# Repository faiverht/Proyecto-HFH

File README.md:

# Proyecto-HFH

## Avance placa primera versión:
Tarjeta de expansión de puertos análogos con conversor análogo digital MCP3424 (4 canales de 18 bits, PGA:1, 2, 4, 8), comunicación I2C dirección I2C (default): 1101

## Frontal

## Trasera

## Otras

## Terminado

## Configuración de Jumpers para fuente de alimetación

Alimentación de voltaje configurable:

1 - Desde la placa arduino Uno 5V (Jumper JP_VDC1 cualquiera o sin conexión y jumper V_IN1 en posición 'INO 5V')

2 - Desde fuente externa mediante Jack 12V (Jumper JP_VDC1  en posición '12V JACK' y jumper V_IN1 en posición 'REG 5V')

3 - Desde fuente externa mediante bornera 12V (Jumper JP_VDC1  en posición '12V EXT' y jumper V_IN1 en posición 'REG 5V')

Adicionalmente los conectores J2, J3 y J4 tienen alimentación configurable de 5V o 12V según posición de los jumpers DC2, DC3 y DC4

**Nota:**

El conector J1 se utiliza exclusivamente para sensor de entrada con alimentación de 6V

## Tarjeta de expansión terminada y en funcionamiento
EL código de prueba para Arduino se encuentran disponibles en /Arduino/Code pruebas de este mismo repositorio

Arduino y tarjeta de expansión

Montajes

Prueba de montaje y adquisición con sensor de gas MQ4

## Proyecto de monitoreo y control con Arduino y/o Raspberry Pi y/o PC (Win - Linux)

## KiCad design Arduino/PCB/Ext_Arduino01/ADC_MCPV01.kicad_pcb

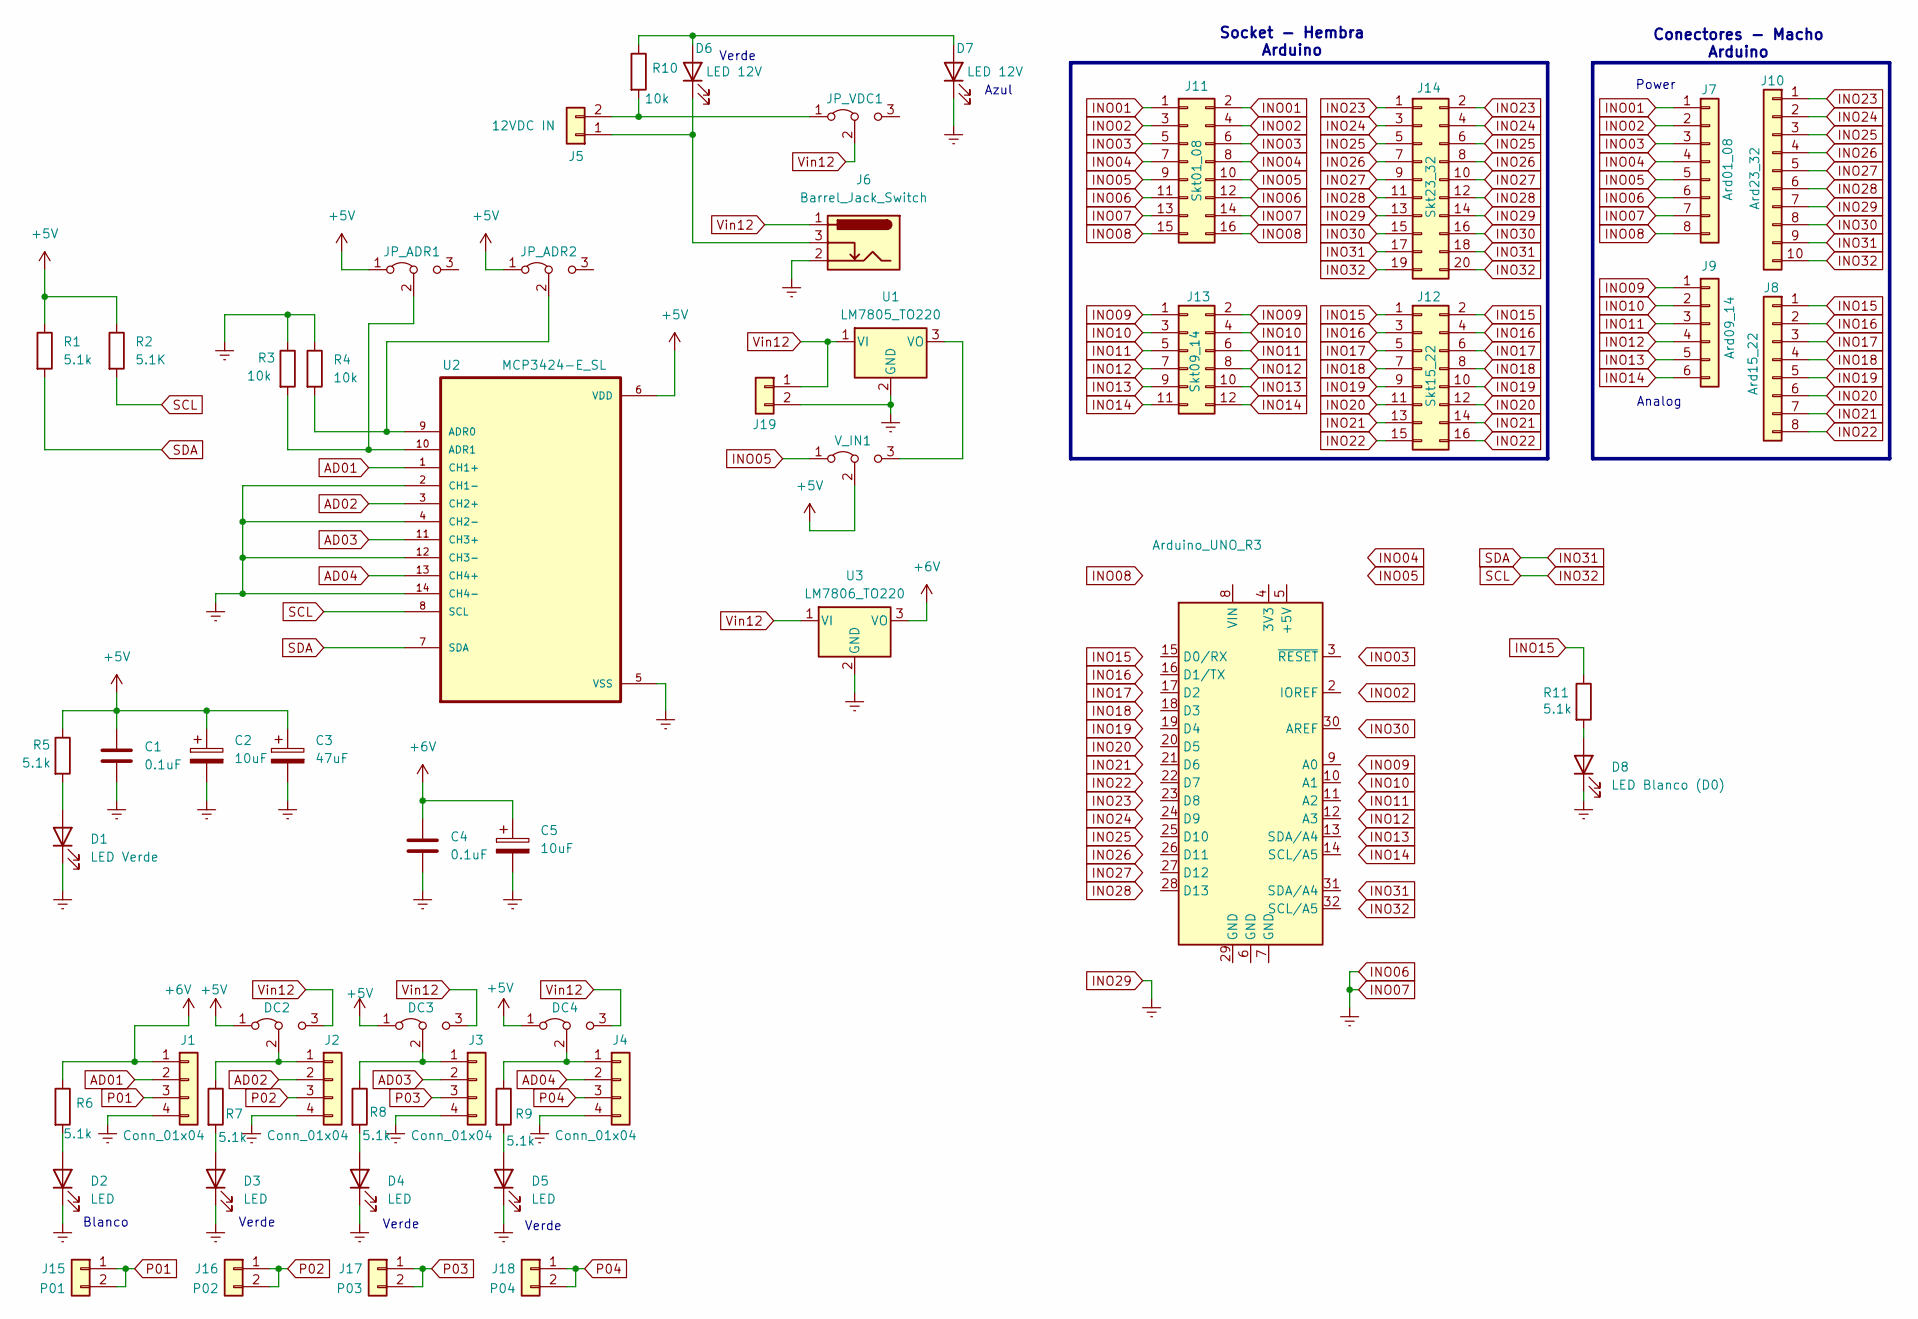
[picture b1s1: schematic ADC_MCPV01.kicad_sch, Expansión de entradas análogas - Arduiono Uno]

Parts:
A1: Arduino_UNO_R3
C1, C4: 0.1uF; C_0603_1608Metric
C2, C5: 10uF; C_1206_3216Metric
C3: 47uF; CP_Elec_6.3x5.9
D1: LED Verde; LED_0603_1608Metric_Pad1.05x0.95mm_HandSolder
D2, D3, D4, D5: LED; LED_0603_1608Metric_Pad1.05x0.95mm_HandSolder
D6, D7: LED 12V; LED_0603_1608Metric_Pad1.05x0.95mm_HandSolder
D8: LED Blanco (D0); LED_0603_1608Metric_Pad1.05x0.95mm_HandSolder
DC2, DC3, DC4: Jumper_3_Bridged12; PinHeader_1x03_P2.54mm_Vertical
J1, J2, J3, J4: Conn_01x04; Molex_KK-254_AE-6410-04A_1x04_P2.54mm_Vertical
J5: 12VDC IN; TerminalBlock_Phoenix_MKDS-1,5-2-5.08_1x02_P5.08mm_Horizont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
J6: Barrel_Jack_Switch; BarrelJack_Horizontal
J7: Ard01_08; PinHeader_1x08_P2.54mm_Vertical
J8: Ard15_22; PinHeader_1x08_P2.54mm_Vertical
J9: Ard09_14; PinHeader_1x06_P2.54mm_Vertical
J10: Ard23_32; PinHeader_1x10_P2.54mm_Vertical
J11: Skt01_08; PinSocket_2x08_P2.54mm_Vertical
J12: Skt15_22; PinSocket_2x08_P2.54mm_Vertical
J13: Skt09_14; PinSocket_2x06_P2.54mm_Vertical
J14: Skt23_32; PinSocket_2x10_P2.54mm_Vertical
J15: P01; PinSocket_1x02_P2.54mm_Vertical
J16: P02; PinSocket_1x02_P2.54mm_Vertical
J17: P03; PinSocket_1x02_P2.54mm_Vertical
J18: P04; PinSocket_1x02_P2.54mm_Vertical
J19: 12VDC IN; PinSocket_1x02_P2.54mm_Vertical
JP_ADR1, JP_ADR2: Jumper_3_Bridged12; PinHeader_1x03_P2.54mm_Vertical
JP_VDC1: Jumper_3_Bridged12; PinHeader_1x03_P2.54mm_Vertical
R1, R5, R6, R7, R8, R9, R11: 5.1k; R_1206_3216Metric
R2: 5.1K; R_1206_3216Metric
R3, R4, R10: 10k; R_1206_3216Metric
U1: LM7805_TO220; TO229P990X238-3N
U2: MCP3424-E_SL; SOIC-14_3.9x8.7mm_P1.27mm; DigiKey_Part_Number MCP3424-E/SL-ND
U3: LM7806_TO220; TO-220-3_Vertical
V_IN1: Jumper_3_Bridged12; PinHeader_1x03_P2.54mm_Vertical

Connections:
+5V: C1.1, C2.1, C3.1, DC2.1 (A), DC3.1 (A), DC4.1 (A), JP_ADR1.1 (A), JP_ADR2.1 (A), R1.1, R2.1, R5.1, U2.6 (VDD), V_IN1.2 (C)
+6V: C4.1, C5.1, J1.1, R6.1, U3.3 (VO)
AD01: J1.2, U2.1 (CH1+)
AD02: J2.2, U2.3 (CH2+)
AD03: J3.2, U2.11 (CH3+)
AD04: J4.2, U2.13 (CH4+)
INO01: J7.1, J11.1, J11.2
INO02: J7.2, J11.3, J11.4
INO03: J7.3, J11.5, J11.6
INO04: J7.4, J11.7, J11.8
INO05: J7.5, J11.9, J11.10, V_IN1.1 (A)
INO06: C1.2, C2.2, C3.2, C4.2, C5.2, D1.1 (K), D2.1 (K), D3.1 (K), D4.1 (K), D5.1 (K), D7.1 (K), D8.1 (K), J1.4, J2.4, J3.4, J4.4, J6.2, J7.6, J7.7, J10.7, J11.11, J11.12, J11.13, J11.14, J14.13, J14.14, J19.2, R3.1, R4.1, U1.2 (GND), U2.2 (CH1-), U2.4 (CH2-), U2.5 (VSS), U2.12 (CH3-), U2.14 (CH4-), U3.2 (GND)
INO08: J7.8, J11.15, J11.16
INO09: J9.1, J13.1, J13.2
INO10: J9.2, J13.3, J13.4
INO11: J9.3, J13.5, J13.6
INO12: J9.4, J13.7, J13.8
INO13: J9.5, J13.9, J13.10
INO14: J9.6, J13.11, J13.12
INO15: J8.1, J12.1, J12.2, R11.1
INO16: J8.2, J12.3, J12.4
INO17: J8.3, J12.5, J12.6
INO18: J8.4, J12.7, J12.8
INO19: J8.5, J12.9, J12.10
INO20: J8.6, J12.11, J12.12
INO21: J8.7, J12.13, J12.14
INO22: J8.8, J12.15, J12.16
INO23: J10.1, J14.1, J14.2
INO24: J10.2, J14.3, J14.4
INO25: J10.3, J14.5, J14.6
INO26: J10.4, J14.7, J14.8
INO27: J10.5, J14.9, J14.10
INO28: J10.6, J14.11, J14.12
INO30: J10.8, J14.15, J14.16
INO31: J10.9, J14.17, J14.18, R1.2, U2.7 (SDA)
INO32: J10.10, J14.19, J14.20, R2.2, U2.8 (SCL)
unnamed: D1.2 (A), R5.2
unnamed: D2.2 (A), R6.2
unnamed: D3.2 (A), R7.2
unnamed: D4.2 (A), R8.2
unnamed: D5.2 (A), R9.2
unnamed: D6.2 (A), D7.2 (A), R10.1
unnamed: D6.1 (K), J5.1, J6.3
unnamed: D8.2 (A), R11.2
unnamed: DC2.2 (C), J2.1, R7.1
unnamed: DC3.2 (C), J3.1, R8.1
unnamed: DC4.2 (C), J4.1, R9.1
unnamed: J5.2, JP_VDC1.1 (A), R10.2
unnamed: JP_ADR1.2 (C), R3.2, U2.10 (ADR1)
unnamed: JP_ADR2.2 (C), R4.2, U2.9 (ADR0)
unnamed: U1.3 (VO), V_IN1.3 (B)
P01: J1.3, J15.1, J15.2
P02: J2.3, J16.1, J16.2
P03: J3.3, J17.1, J17.2
P04: J4.3, J18.1, J18.2
Vin12: DC2.3 (B), DC3.3 (B), DC4.3 (B), J6.1, J19.1, JP_VDC1.2 (C), U1.1 (VI), U3.1 (VI)

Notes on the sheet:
Analog
Verde
Blanco
Azul
Power
Socket - Hembra Arduino
Conectores - Macho Arduino

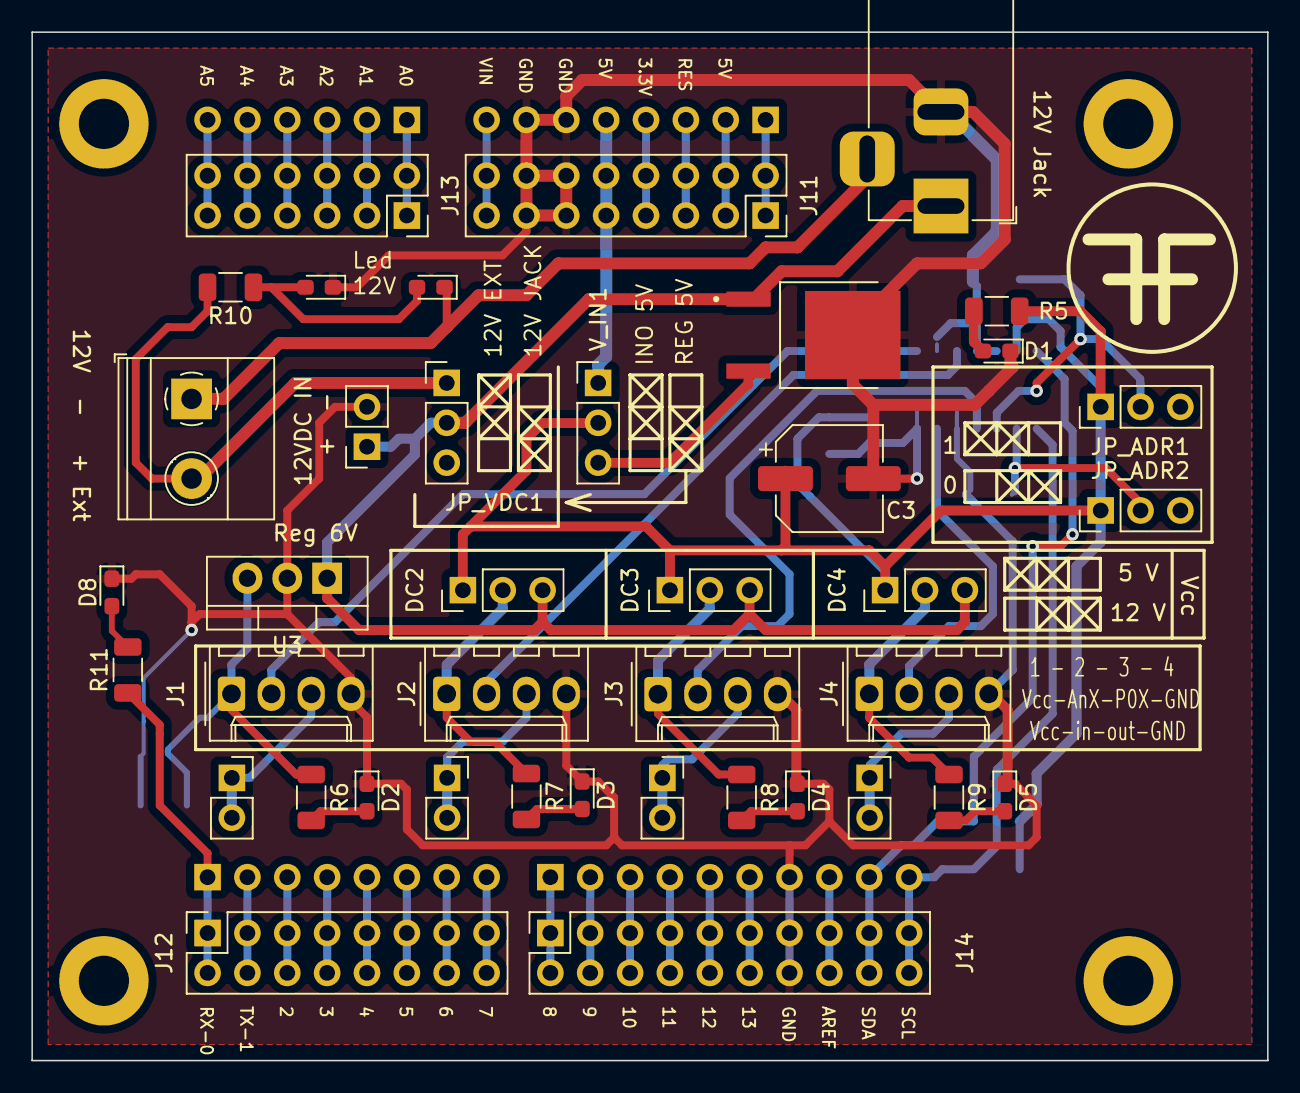
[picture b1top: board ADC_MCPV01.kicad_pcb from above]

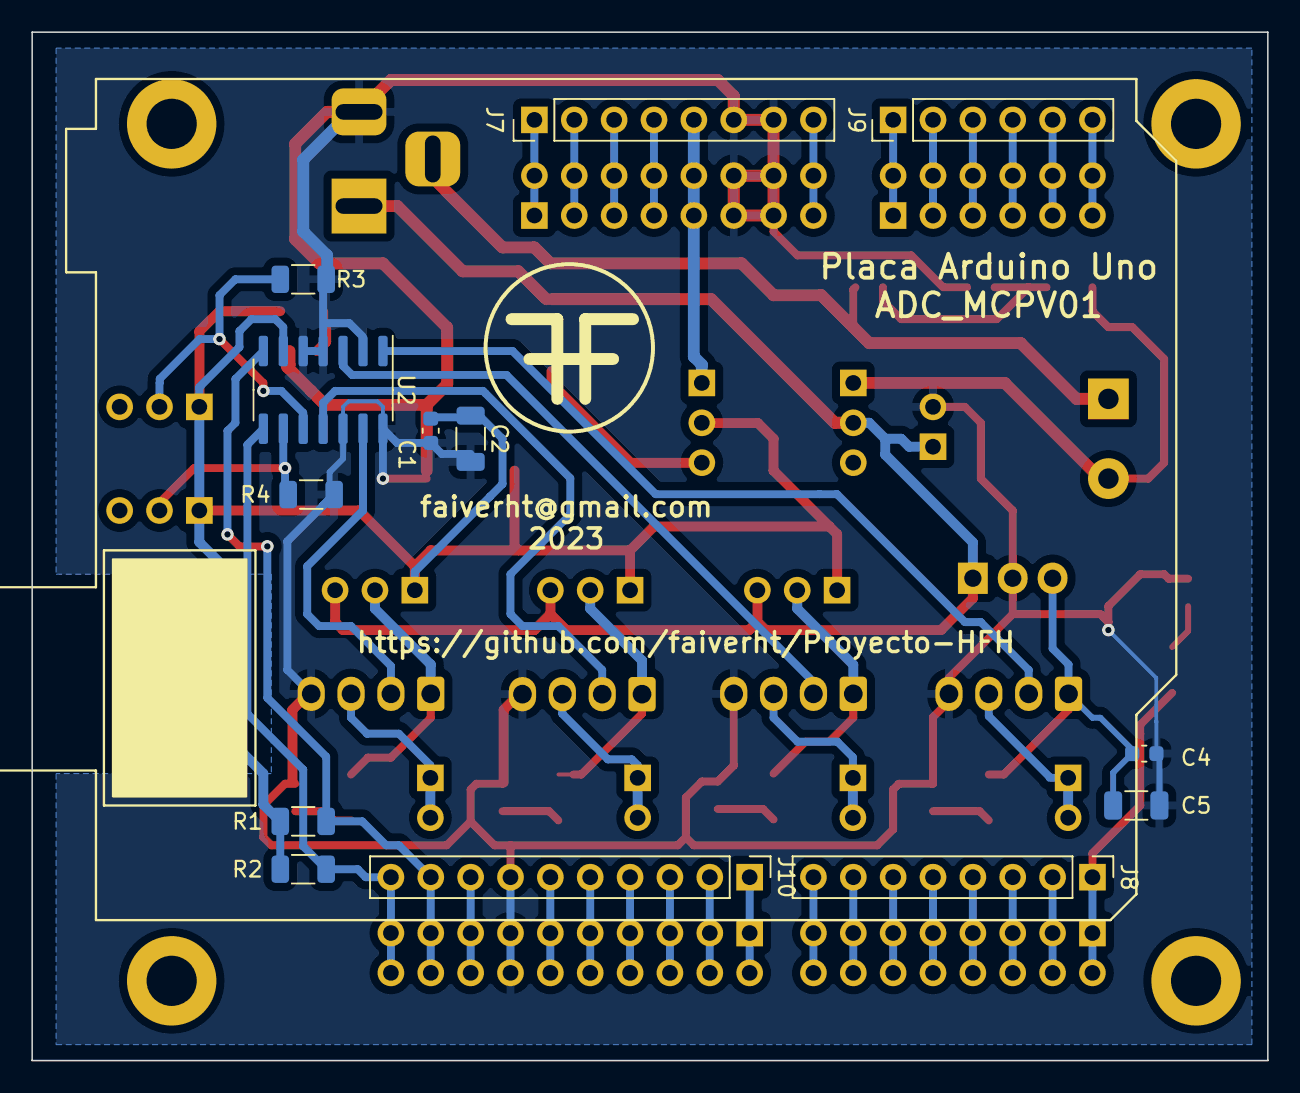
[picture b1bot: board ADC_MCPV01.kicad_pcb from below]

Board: 2 copper layers, 78.7 x 65.5 mm, 53 parts (13 on the bottom side), 56 nets.

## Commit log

2023-05-15 Se adiciona archivo de informaciones general del proyecto
    Links, recomendaciones ...
2023-05-15 Resumen de códigos realizados
    Listado, comentarios y recomendaciones acerca de todos los códigos realizados
2023-05-16 LCD_01
    Prueba de funcionamiento LCD con I2C
2023-05-16 LCD_02_ADC
    Visualización en LCD (I2C) de lectura análoga en A0
2023-05-16 LCD_03_MQ4
    Visualización en LCD (I2C) de voltaje análogo (10 bits) capturado desde sensor MQ4
2023-05-16 LCD_03_MQ4_ppm
    Por ahora similar a LCD_03_MQ4.ino
2023-05-16 adicionando MQ4 ppm
2023-05-31 Corregido mayo
    Actualizado con lectura en ppm
2023-05-31 Create MQ4_ppm_Ok.ino
    Aplicando ecuación según gráficas de datasheet MQ4 paga metano solamente
2023-11-20 Update Infos FHF.txt
    Adicionando proyecto Kicad para Arduino uno
2023-11-20 Create info.txt
    void
2023-11-20 Add files via upload
    vesión 01
2023-11-20 Add files via upload
    Imágenes PCB MCP
2023-11-20 Update README.md
    actualizando imágenes PCB
2023-11-20 Update README.md
    corrigiendo nombre de archivo imágenes sin espacio
2023-11-20 Add files via upload
    Actualizando imágenes con nombre sin espacio
2023-11-20 Update README.md
    Actulización de contenido nov20
2023-11-20 Update Resumen info.txt
    correción de forma
2023-11-20 Update Resumen info.txt
    corrección de forma 2
2023-11-20 Add files via upload
    PDFs
2023-11-20 Add files via upload
    Gerber files
2023-11-21 Actualizando
2023-11-21 actualizando imgs
2023-11-22 actualizar img06 JP-DC
2023-11-22 Update README.md
    add img 06
2023-11-22 actualizar img01-4
2023-11-25 actualizando kicad
2024-02-22 Add files via upload
    Pcb terminado
2024-02-22 Update README.md
    Adicionando imgs pcb terminado
2024-02-22 Add files via upload
    Subiendo pantallazos de código
2024-02-26 En producción
